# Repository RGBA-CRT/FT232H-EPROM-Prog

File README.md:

# FT232H-EPROM-Prog
+ USB 27C322 EPROM Programmer with FT232H.
+ software and hardware.
+ only supports 27C322.
+ *THIS REPOSITORY IS FOR EXPERIMENTAL PURPOSES.* all function is work in progress.
+ このリポジトリの内容はすべて個人的な実験目的です。コードや回路を読める方以外は利用をお勧めできません。

# About 2017
- FT232Hを使ったEPROMライタ(プログラマ)
- 数点の部品で作れるので、高価なEPROMライタがいらない
- EEPROM, FlashMemoryには**未対応**
- シリアルEEPROM, PICには非対応
- 27C322と27C160で動作確認
- **現在テストプログラムの段階**
- ビルドには[こちらの[AB-FT232HLib]](https://github.com/RGBA-CRT/AB-FT232HLib)が必要

## 回路
pcbディレクトリを見てください。
[回路図PDF](pcb/kairo_v2.1b.pdf)

## 関連リポジトリ
+ 27C322 x2基板
  + https://github.com/RGBA-CRT/RGBA_CRT_ROM_BOARD
+ FT232H制御ライブラリ for ActiveBasic
   + https://github.com/RGBA-CRT/AB-FT232HLib

----
Programmed by RGBA_CRT 2017-2023  
Project url: https://github.com/RGBA-CRT/FT232H-EPROM-Prog

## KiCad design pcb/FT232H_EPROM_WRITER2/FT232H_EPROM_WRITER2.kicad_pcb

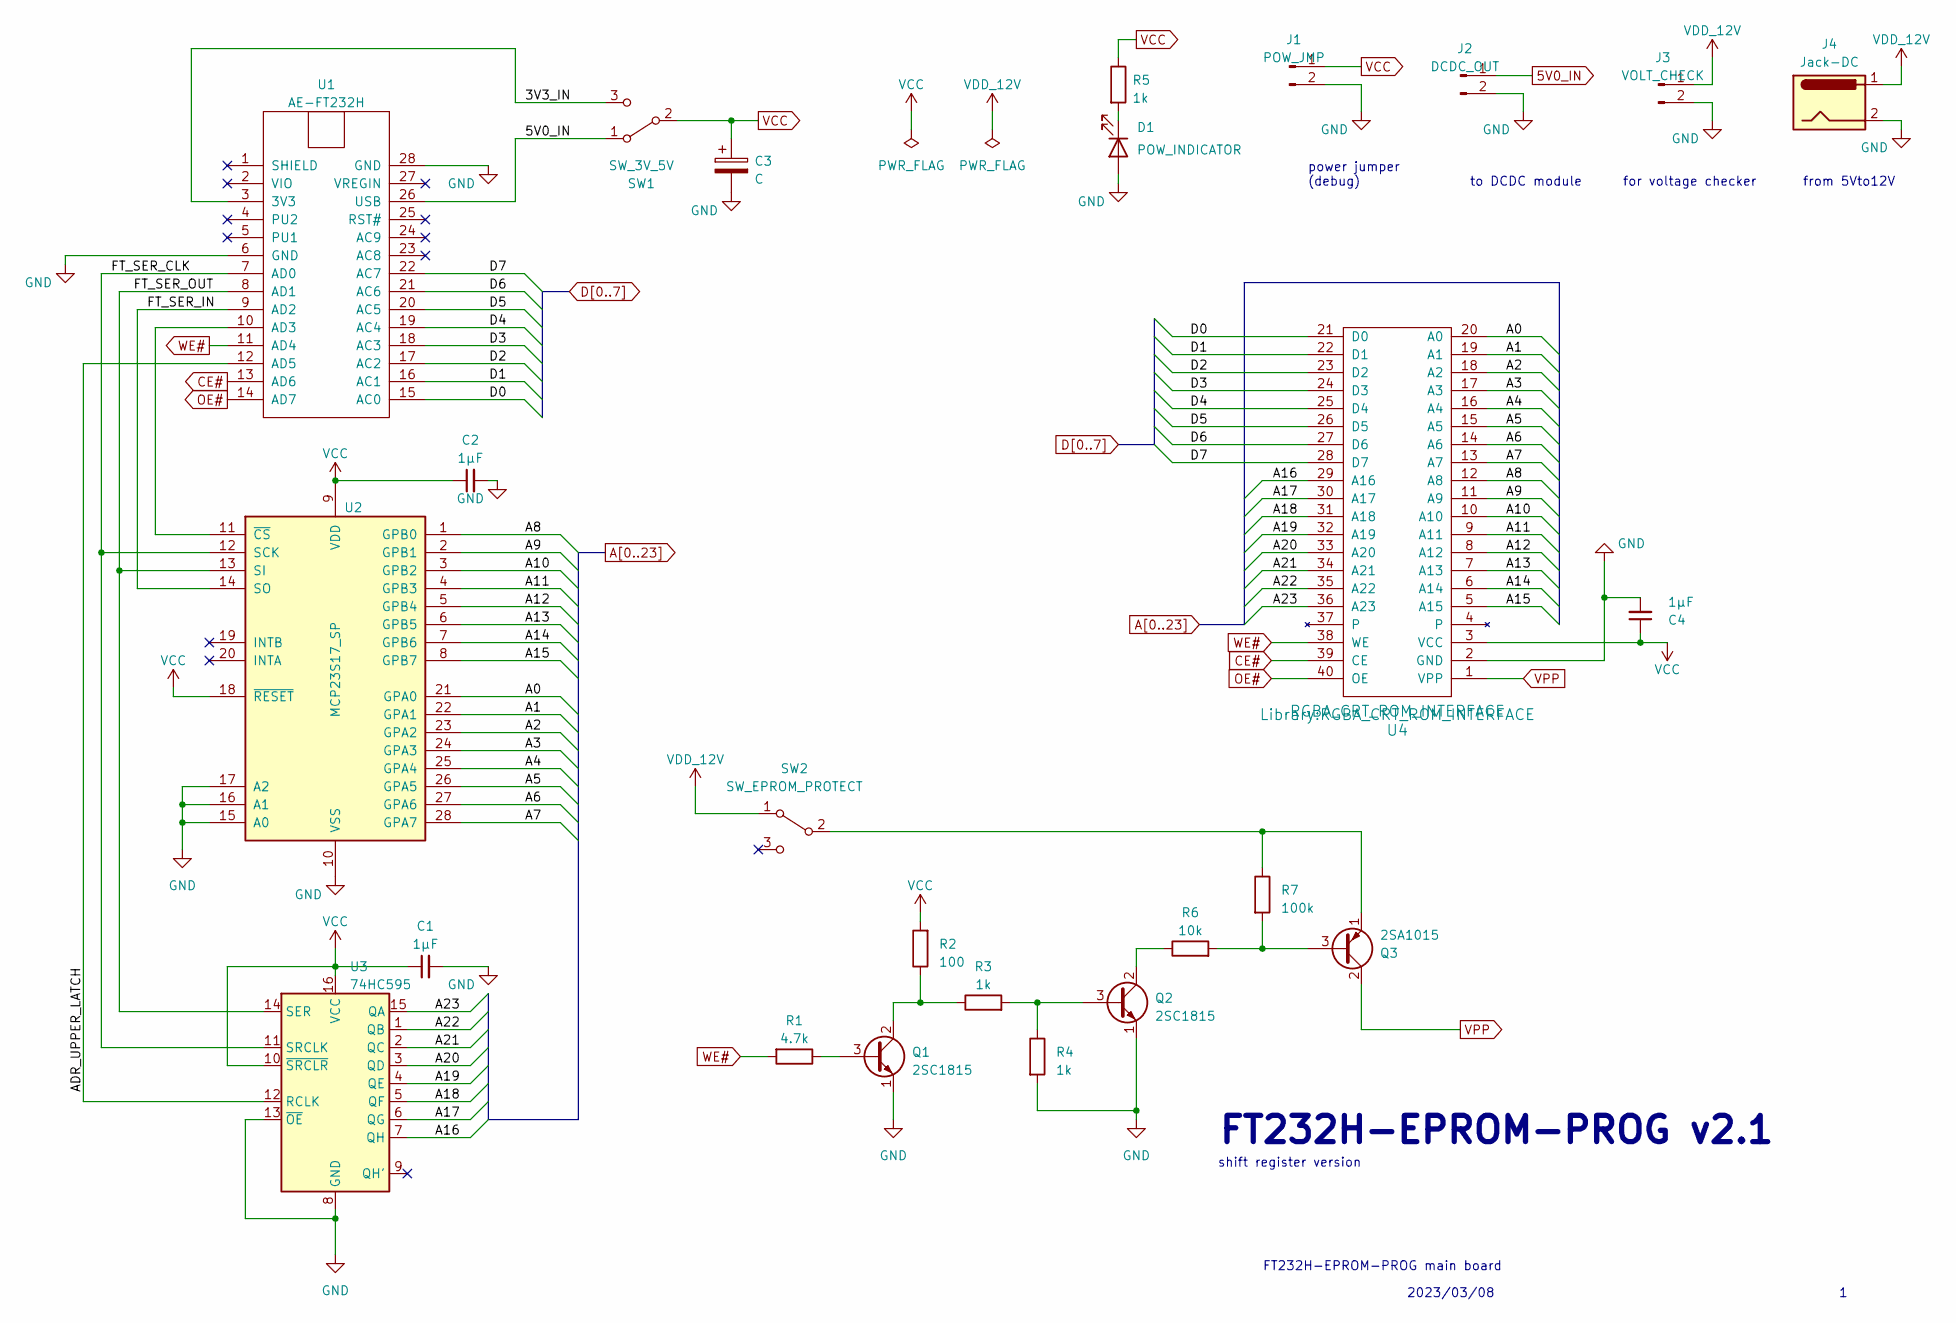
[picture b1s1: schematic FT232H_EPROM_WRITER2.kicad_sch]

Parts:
C1: 1μF; C_Disc_D4.3mm_W1.9mm_P5.00mm
C2, C4: 1μF; C_Disc_D3.4mm_W2.1mm_P2.50mm
C3: C; C_Radial_D5.0mm_H5.0mm_P2.00mm
D1: POW_INDICATOR; LED_D2.0mm_W4.0mm_H2.8mm_FlatTop
J1: POW_JMP; PinHeader_2x01_P2.54mm_Vertical
J2: DCDC_OUT; PinHeader_2x01_P2.54mm_Vertical
J3: VOLT_CHECK; PinHeader_2x01_P2.54mm_Vertical
J4: Jack-DC; PinHeader_2x01_P2.54mm_Vertical
Q1, Q2: 2SC1815; TO-92_Inline_Wide
Q3: 2SA1015; TO-92_Inline_Wide
R1: 4.7k; R_Axial_DIN0204_L3.6mm_D1.6mm_P2.54mm_Vertical
R2: 100; R_Axial_DIN0204_L3.6mm_D1.6mm_P2.54mm_Vertical
R3, R4, R5: 1k; R_Axial_DIN0204_L3.6mm_D1.6mm_P2.54mm_Vertical
R6: 10k; R_Axial_DIN0204_L3.6mm_D1.6mm_P2.54mm_Vertical
R7: 100k; R_Axial_DIN0204_L3.6mm_D1.6mm_P2.54mm_Vertical
SW1: SW_3V_5V; PinHeader_1x03_P2.54mm_Vertical
SW2: SW_EPROM_PROTECT; PinHeader_1x03_P2.54mm_Vertical
U1: AE-FT232H; DIP-28_W15.24mm
U2: MCP23S17_SP; DIP-28_W7.62mm
U3: 74HC595; DIP-16_W7.62mm
U4: RGBA_CRT_ROM_INTERFACE

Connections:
5V0_IN: J2.1, SW1.1 (A), U1.26 (USB)
/3V3_IN: SW1.3 (C), U1.3 (3V3)
/ADR_UPPER_LATCH: U1.12 (AD5), U3.12 (RCLK)
/FT_SER_CLK: U1.7 (AD0), U2.12 (SCK), U3.11 (SRCLK)
/FT_SER_IN: U1.9 (AD2), U2.14 (SO)
/FT_SER_OUT: U1.8 (AD1), U2.13 (SI), U3.14 (SER)
A0: U2.21 (GPA0), U4.20 (A0)
A1: U2.22 (GPA1), U4.19 (A1)
A2: U2.23 (GPA2), U4.18 (A2)
A3: U2.24 (GPA3), U4.17 (A3)
A4: U2.25 (GPA4), U4.16 (A4)
A5: U2.26 (GPA5), U4.15 (A5)
A6: U2.27 (GPA6), U4.14 (A6)
A7: U2.28 (GPA7), U4.13 (A7)
A8: U2.1 (GPB0), U4.12 (A8)
A9: U2.2 (GPB1), U4.11 (A9)
A10: U2.3 (GPB2), U4.10 (A10)
A11: U2.4 (GPB3), U4.9 (A11)
A12: U2.5 (GPB4), U4.8 (A12)
A13: U2.6 (GPB5), U4.7 (A13)
A14: U2.7 (GPB6), U4.6 (A14)
A15: U2.8 (GPB7), U4.5 (A15)
A16: U3.7 (QH), U4.29 (A16)
A17: U3.6 (QG), U4.30 (A17)
A18: U3.5 (QF), U4.31 (A18)
A19: U3.4 (QE), U4.32 (A19)
A20: U3.3 (QD), U4.33 (A20)
A21: U3.2 (QC), U4.34 (A21)
A22: U3.1 (QB), U4.35 (A22)
A23: U3.15 (QA), U4.36 (A23)
CE#: U1.13 (AD6), U4.39 (CE)
D0: U1.15 (AC0), U4.21 (D0)
D1: U1.16 (AC1), U4.22 (D1)
D2: U1.17 (AC2), U4.23 (D2)
D3: U1.18 (AC3), U4.24 (D3)
D4: U1.19 (AC4), U4.25 (D4)
D5: U1.20 (AC5), U4.26 (D5)
D6: U1.21 (AC6), U4.27 (D6)
D7: U1.22 (AC7), U4.28 (D7)
GND: C1.2, C2.2, C3.2, C4.2, D1.2 (A), J1.2, J2.2, J3.2, J4.2, Q1.1 (E), Q2.1 (E), R4.2, U1.6 (GND), U1.28 (GND), U2.10 (VSS), U2.15 (A0), U2.16 (A1), U2.17 (A2), U3.8 (GND), U3.13 (~OE), U4.2 (GND)
unnamed: D1.1 (K), R5.2
unnamed: Q1.3 (B), R1.1
unnamed: Q1.2 (C), R2.1, R3.1
unnamed: Q2.3 (B), R3.2, R4.1
unnamed: Q2.2 (C), R6.1
unnamed: Q3.3 (B), R6.2, R7.2
unnamed: Q3.1 (E), R7.1, SW2.2 (B)
unnamed: U1.10 (AD3), U2.11 (~CS)
OE#: U1.14 (AD7), U4.40 (OE)
VCC: C1.1, C2.1, C3.1, C4.1, J1.1, R2.2, R5.1, SW1.2 (B), U2.9 (VDD), U2.18 (~RESET), U3.10 (~SRCLR), U3.16 (VCC), U4.3 (VCC)
VDDA: J3.1, J4.1, SW2.1 (A)
VPP: Q3.2 (C), U4.1 (VPP)
WE#: R1.2, U1.11 (AD4), U4.38 (WE)

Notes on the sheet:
FT232H-EPROM-PROG main board
to DCDC module
from 5Vto12V
FT232H-EPROM-PROG v2.1
power jumper (debug)
shift register version
for voltage checker
2023/03/08

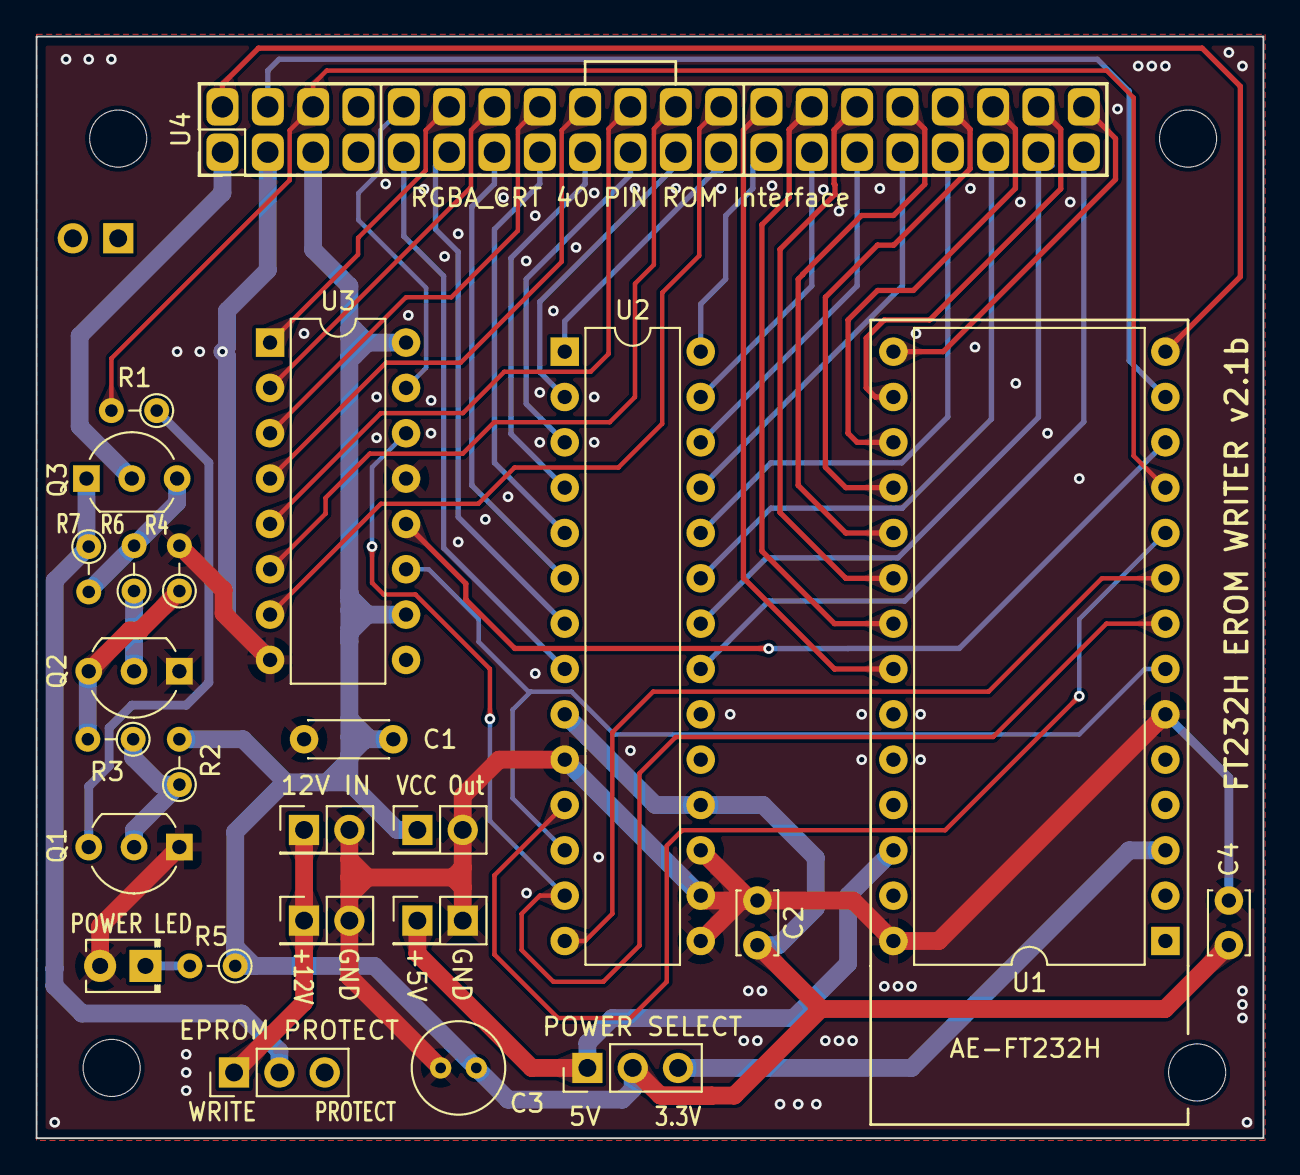
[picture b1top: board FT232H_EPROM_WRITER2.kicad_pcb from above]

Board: 2 copper layers, 68.7 x 61.7 mm, 30 parts (1 on the bottom side), 53 nets.

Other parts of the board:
GND_PIN: PinHeader_1x02_P2.54mm_Vertical
MOUNT1, MOUNT1#2, MOUNT1#3, MOUNT1#4: MountingHole_3.2mm_M3

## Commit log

2017-07-27 "高速化"
2018-09-13 ui fix, WE logic fix
2021-02-14 reduce Write opration commands
2023-04-09 WIP: PCBv2
2023-06-19 Impl: PCBv2
2023-06-24 improbe write error screen.
2023-06-24 Add kicad files.
2023-06-24 add ft232h_config_eprom.xml
2023-06-24 add sch pdf
2023-07-02 Create LICENSE
2024-02-12 update for 27C801
2024-03-20 Show dump when bankd cmd fail
